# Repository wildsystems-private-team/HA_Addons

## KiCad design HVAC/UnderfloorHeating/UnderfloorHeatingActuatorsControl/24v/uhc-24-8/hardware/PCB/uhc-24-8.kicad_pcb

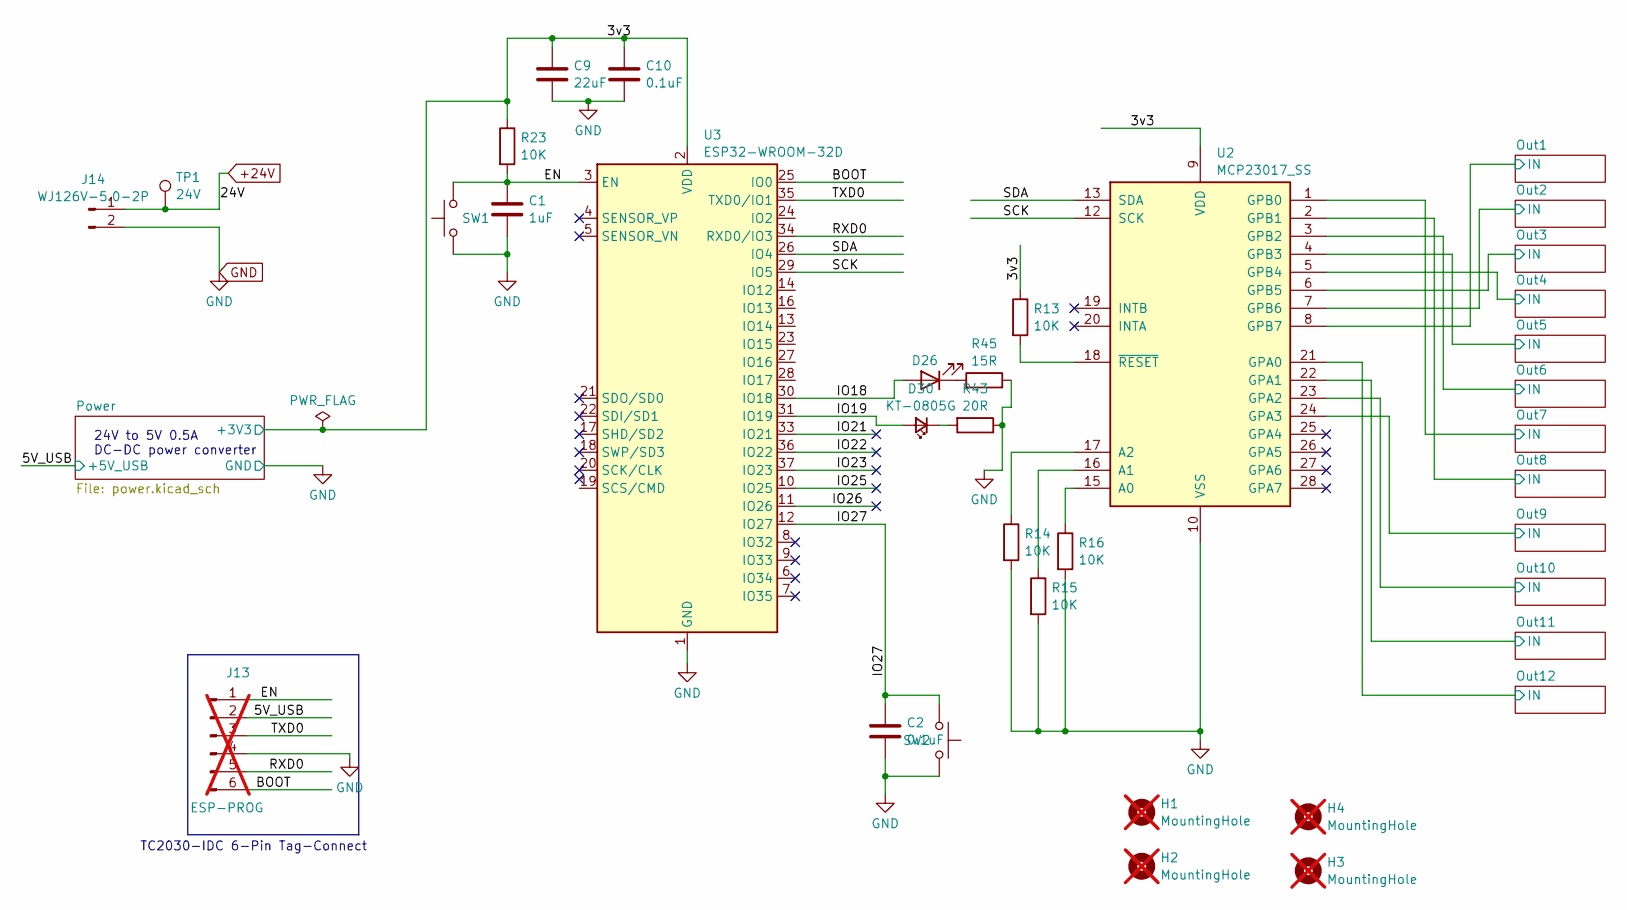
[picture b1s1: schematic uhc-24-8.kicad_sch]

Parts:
C1: 1uF; C_0402_1005Metric; LCSC Part # C14445
C2, C10: 0.1uF; C_0402_1005Metric; LCSC Part # C541406
C9: 22uF; C_0603_1608Metric; LCSC Part # C59461
D26: KT-0805B; D_0805_2012Metric; LCSC Part # C2293
D30: KT-0805G; LED_0805_2012Metric; LCSC Part # C2297
H1, H2, H3, H4: MountingHole; MountingHole_3.2mm_M3; not fitted
J13: ESP-PROG; Tag-Connect_TC2030-IDC-FP_2x03_P1.27mm_Vertical; not fitted
J14: WJ126V-5.0-2P; CONN-TH_2P-P5.08_DIBO_DB142V-5.08-2P; LCSC Part # C2898699
R13, R14, R15, R16, R23: 10K; R_0603_1608Metric; LCSC Part # C25804
R43: 20R; R_0805_2012Metric; LCSC Part # C17659
R45: 15R; R_0805_2012Metric
SW1: Reboot; SW-SMD_4P-L5.1-W5.1-P3.70-LS6.5-TL-2; LCSC Part # C318884
SW2: Clear; SW-SMD_4P-L5.1-W5.1-P3.70-LS6.5-TL-2; LCSC Part # C318884
TP1: 24V; TestPoint_Pad_D2.0mm
U2: MCP23017_SS; SSOP-28_5.3x10.2mm_P0.65mm; LCSC Part # C558584
U3: ESP32-WROOM-32D; WIFI-SMD_ESP32-WROOM-32E-A; LCSC Part # C701341

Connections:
+24V: J14.1, TP1.1; also elsewhere on the board
/3v3: C9.1, C10.1, R13.1, R23.1, U2.9 (VDD), U3.2 (VDD); also elsewhere on the board
/5V_USB: J13.2; also elsewhere on the board
/BOOT: J13.6, U3.25 (IO0)
/EN: C1.1, J13.1, R23.2, SW1.2, U3.3 (EN)
/IO18: D26.2 (A), U3.30 (IO18)
/IO19: D30.2 (A), U3.31 (IO19)
/IO21: U3.33 (IO21)
/IO22: U3.36 (IO22)
/IO23: U3.37 (IO23)
/IO25: U3.10 (IO25)
/IO26: U3.11 (IO26)
/IO27: C2.1, SW2.2, U3.12 (IO27)
/Out1/IN: U2.8 (GPB7); also elsewhere on the board
/Out2/IN: U2.7 (GPB6); also elsewhere on the board
/Out3/IN: U2.6 (GPB5); also elsewhere on the board
/Out4/IN: U2.5 (GPB4); also elsewhere on the board
/Out5/IN: U2.4 (GPB3); also elsewhere on the board
/Out6/IN: U2.3 (GPB2); also elsewhere on the board
/Out7/IN: U2.1 (GPB0); also elsewhere on the board
/Out8/IN: U2.2 (GPB1); also elsewhere on the board
/Out9/IN: U2.24 (GPA3); also elsewhere on the board
/Out10/IN: U2.23 (GPA2); also elsewhere on the board
/Out11/IN: U2.22 (GPA1); also elsewhere on the board
/Out12/IN: U2.21 (GPA0); also elsewhere on the board
/RXD0: J13.5, U3.34 (RXD0/IO3)
/SCK: U2.12 (SCK), U3.29 (IO5)
/SDA: U2.13 (SDA), U3.26 (IO4)
/TXD0: J13.3, U3.35 (TXD0/IO1)
GND: C1.2, C2.2, C9.2, C10.2, J13.4, J14.2, R14.2, R15.2, R16.2, R43.1, R45.2, SW1.1, SW2.1, U2.10 (VSS), U3.1 (GND), U3.15 (GND), U3.38 (GND), U3.39 (GND); also elsewhere on the board
unnamed: D26.1 (K), R45.1
unnamed: D30.1 (K), R43.2
unnamed: R16.1, U2.15 (A0)
unnamed: R15.1, U2.16 (A1)
unnamed: R14.1, U2.17 (A2)
unnamed: R13.2, U2.18 (~RESET)

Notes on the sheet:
24V to 5V 0.5A DC-DC power converter
TC2030-IDC 6-Pin Tag-Connect

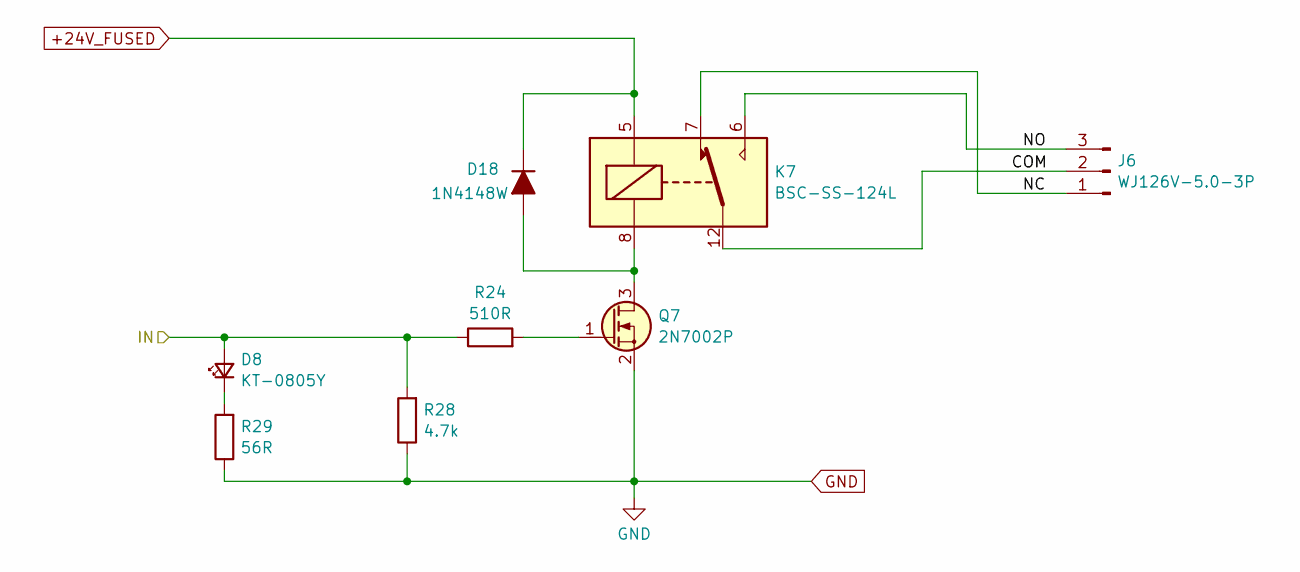
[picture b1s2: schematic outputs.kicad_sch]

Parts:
D8: KT-0805Y; LED_0805_2012Metric; LCSC Part # C2296
D18: 1N4148W; D_SOD-123; LCSC Part # C81598
J6: WJ126V-5.0-3P; CONN-TH_3P-P5.08_DIBO_DB142V-5.08-3P; LCSC Part # C2898700
K7: BSC-SS-124L; Relay_SPDT_QLRELAY_BSC; LCSC Part # C22384984
Q7: 2N7002P; SOT-23; LCSC Part # C81488
R24: 510R; R_0805_2012Metric; LCSC Part # C17734
R28: 4.7k; R_0805_2012Metric; LCSC Part # C17673
R29: 56R; R_0805_2012Metric; LCSC Part # C17757

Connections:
+24V_FUSED: D18.1 (K), K7.5; also elsewhere on the board
/Out7/COM: J6.2, K7.12
/Out7/IN: D8.2 (A), R24.1, R28.2; also elsewhere on the board
/Out7/NC: J6.1, K7.7
/Out7/NO: J6.3, K7.6
GND: Q7.2 (S), R28.1, R29.1; also elsewhere on the board
unnamed: D8.1 (K), R29.2
unnamed: D18.2 (A), K7.8, Q7.3 (D)
unnamed: Q7.1 (G), R24.2

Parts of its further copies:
D1, D2, D3, D4, D5, D6, D7, D9, D10, D11, D12: KT-0805Y; LED_0805_2012Metric; LCSC Part # C2296
D13, D14, D15, D16, D17, D19, D20, D21, D22, D23, D24: 1N4148W; D_SOD-123; LCSC Part # C81598
J1, J2, J3, J4, J5, J7, J8, J9, J10, J11, J12: WJ126V-5.0-3P; CONN-TH_3P-P5.08_DIBO_DB142V-5.08-3P; LCSC Part # C2898700
K1, K2, K3, K4, K5, K6, K8, K9, K10, K11, K12: BSC-SS-124L; Relay_SPDT_QLRELAY_BSC; LCSC Part # C22384984
Q1, Q2, Q3, Q4, Q5, Q6, Q8, Q9, Q10, Q11, Q12: 2N7002P; SOT-23; LCSC Part # C81488
R1, R6, R7, R11, R17, R20, R26, R30, R34, R36, R41: 510R; R_0805_2012Metric; LCSC Part # C17734
R2, R3, R8, R12, R19, R22, R25, R32, R35, R38, R40: 56R; R_0805_2012Metric; LCSC Part # C17757
R4, R5, R9, R10, R18, R21, R27, R31, R33, R37, R39: 4.7k; R_0805_2012Metric; LCSC Part # C17673

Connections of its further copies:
+24V_FUSED: D13.1 (K), D14.1 (K), D15.1 (K), D16.1 (K), D17.1 (K), D19.1 (K), D20.1 (K), D21.1 (K), D22.1 (K), D23.1 (K), D24.1 (K), K1.5, K2.5, K3.5, K4.5, K5.5, K6.5, K8.5, K9.5, K10.5, K11.5, K12.5; also elsewhere on the board
/Out1/COM: J1.2, K1.12
/Out1/IN: D1.2 (A), R1.1, R5.2; also elsewhere on the board
/Out1/NC: J1.1, K1.7
/Out1/NO: J1.3, K1.6
/Out2/COM: J3.2, K2.12
/Out2/IN: D2.2 (A), R4.2, R6.1; also elsewhere on the board
/Out2/NC: J3.1, K2.7
/Out2/NO: J3.3, K2.6
/Out3/COM: J2.2, K3.12
/Out3/IN: D3.2 (A), R7.1, R9.2; also elsewhere on the board
/Out3/NC: J2.1, K3.7
/Out3/NO: J2.3, K3.6
/Out4/COM: J4.2, K4.12
/Out4/IN: D4.2 (A), R11.1, R18.2; also elsewhere on the board
/Out4/NC: J4.1, K4.7
/Out4/NO: J4.3, K4.6
/Out5/COM: J5.2, K5.12
/Out5/IN: D5.2 (A), R10.2, R17.1; also elsewhere on the board
/Out5/NC: J5.1, K5.7
/Out5/NO: J5.3, K5.6
/Out6/COM: J7.2, K6.12
/Out6/IN: D6.2 (A), R20.1, R21.2; also elsewhere on the board
/Out6/NC: J7.1, K6.7
/Out6/NO: J7.3, K6.6
/Out8/COM: J8.2, K8.12
/Out8/IN: D7.2 (A), R26.1, R27.2; also elsewhere on the board
/Out8/NC: J8.1, K8.7
/Out8/NO: J8.3, K8.6
/Out9/COM: J9.2, K9.12
/Out9/IN: D9.2 (A), R30.1, R31.2; also elsewhere on the board
/Out9/NC: J9.1, K9.7
/Out9/NO: J9.3, K9.6
/Out10/COM: J10.2, K10.12
/Out10/IN: D11.2 (A), R33.2, R36.1; also elsewhere on the board
/Out10/NC: J10.1, K10.7
/Out10/NO: J10.3, K10.6
/Out11/COM: J11.2, K11.12
/Out11/IN: D10.2 (A), R34.1, R37.2; also elsewhere on the board
/Out11/NC: J11.1, K11.7
/Out11/NO: J11.3, K11.6
/Out12/COM: J12.2, K12.12
/Out12/IN: D12.2 (A), R39.2, R41.1; also elsewhere on the board
/Out12/NC: J12.1, K12.7
/Out12/NO: J12.3, K12.6
GND: Q1.2 (S), Q2.2 (S), Q3.2 (S), Q4.2 (S), Q5.2 (S), Q6.2 (S), Q8.2 (S), Q9.2 (S), Q10.2 (S), Q11.2 (S), Q12.2 (S), R2.1, R3.1, R4.1, R5.1, R8.1, R9.1, R10.1, R12.1, R18.1, R19.1, R21.1, R22.1, R25.1, R27.1, R31.1, R32.1, R33.1, R35.1, R37.1, R38.1, R39.1, R40.1; also elsewhere on the board
unnamed: D1.1 (K), R2.2
unnamed: D2.1 (K), R3.2
unnamed: D3.1 (K), R8.2
unnamed: D4.1 (K), R19.2
unnamed: D5.1 (K), R12.2
unnamed: D6.1 (K), R22.2
unnamed: D7.1 (K), R25.2
unnamed: D9.1 (K), R32.2
unnamed: D10.1 (K), R35.2
unnamed: D11.1 (K), R38.2
unnamed: D12.1 (K), R40.2
unnamed: D13.2 (A), K1.8, Q1.3 (D)
unnamed: D14.2 (A), K2.8, Q2.3 (D)
unnamed: D15.2 (A), K3.8, Q3.3 (D)
unnamed: D16.2 (A), K4.8, Q4.3 (D)
unnamed: D17.2 (A), K5.8, Q5.3 (D)
unnamed: D19.2 (A), K6.8, Q6.3 (D)
unnamed: D20.2 (A), K8.8, Q9.3 (D)
unnamed: D21.2 (A), K9.8, Q8.3 (D)
unnamed: D22.2 (A), K10.8, Q10.3 (D)
unnamed: D23.2 (A), K11.8, Q12.3 (D)
unnamed: D24.2 (A), K12.8, Q11.3 (D)
unnamed: Q1.1 (G), R1.2
unnamed: Q2.1 (G), R6.2
unnamed: Q3.1 (G), R7.2
unnamed: Q4.1 (G), R11.2
unnamed: Q5.1 (G), R17.2
unnamed: Q6.1 (G), R20.2
unnamed: Q8.1 (G), R30.2
unnamed: Q9.1 (G), R26.2
unnamed: Q10.1 (G), R36.2
unnamed: Q11.1 (G), R41.2
unnamed: Q12.1 (G), R34.2

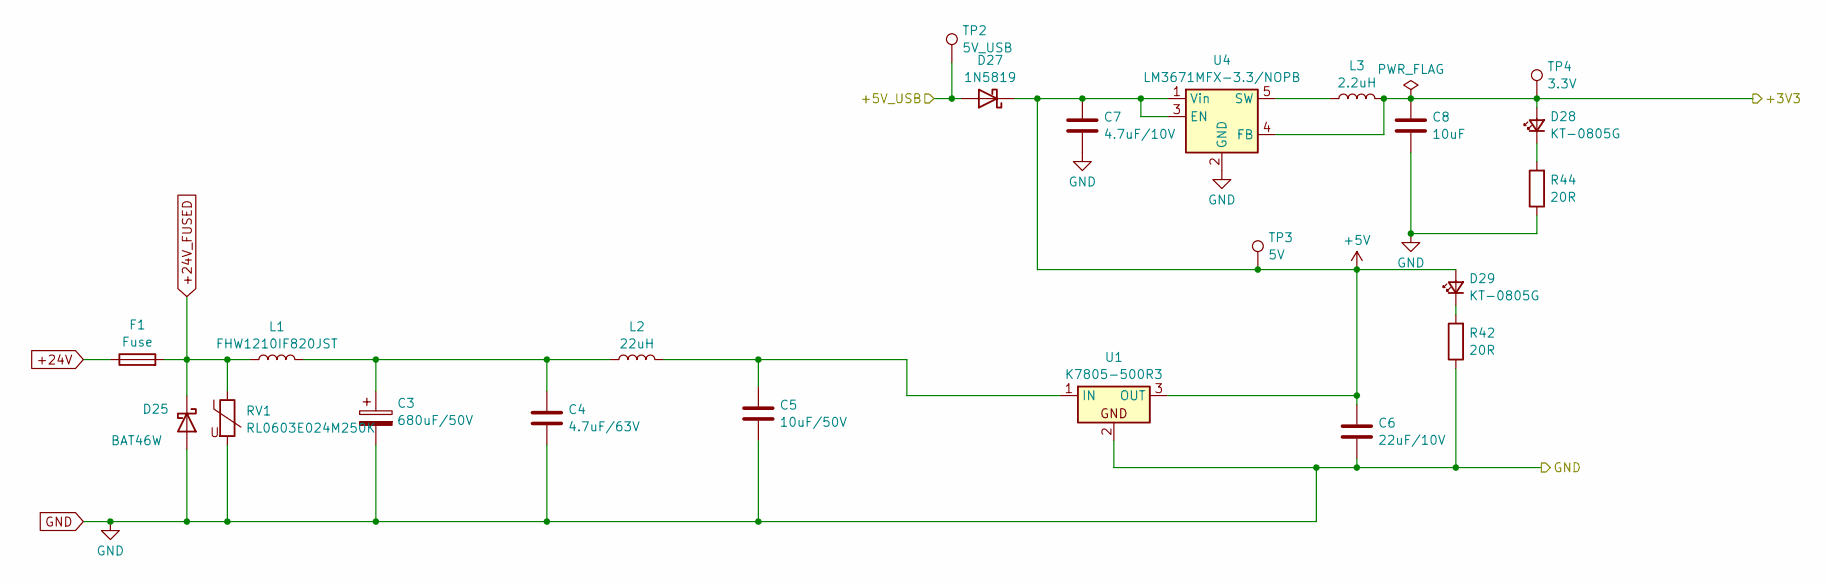
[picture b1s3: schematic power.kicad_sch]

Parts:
C3: 680uF/50V; CAP-SMD_BD12.5-L13.0-W13.0-LS14.4-FD; LCSC Part # C487372
C4: 4.7uF/63V; C_1206_3216Metric; LCSC Part # C29823
C5: 10uF/50V; C_1206_3216Metric; LCSC Part # C13585
C6: 22uF/10V; C_1206_3216Metric; LCSC Part # C5672
C7: 4.7uF/10V; C_0402_1005Metric; LCSC Part # C23733
C8: 10uF; C_0603_1608Metric; LCSC Part # C19702
D25: BAT46W; D_SOD-123; LCSC Part # C7420332
D27: 1N5819; D_SOD-123; JLCPCB Part # C3033976
D28, D29: KT-0805G; LED_0805_2012Metric; LCSC Part # C2297
F1: Fuse; FUSE-TH_L24.4-W9.4-P22.60; LCSC Part # C717030
L1: FHW1210IF820JST; L_1210_3225Metric; LCSC Part # C394099
L2: 22uH; L_0603_1608Metric; LCSC Part # C6808015
L3: 2.2uH; Ferrite_1206_3216Metric; LCSC Part # C139249
R42, R44: 20R; R_0805_2012Metric; LCSC Part # C17659
RV1: RL0603E024M250K; D_0603_1608Metric; LCSC Part # LCSC Part #
TP2: 5V_USB; TestPoint_Pad_D2.0mm
TP3: 5V; TestPoint_Pad_D2.0mm
TP4: 3.3V; TestPoint_Pad_D2.0mm
U1: K7805-500R3; PWRM-TH_K78XX-500R3; LCSC Part # C909662
U4: LM3671MFX-3.3/NOPB; TSOT-23-5; LCSC Part # C477918

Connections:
+5V: C6.1, C7.1, D27.1 (K), D29.2 (A), TP3.1, U1.3 (OUT), U4.1 (Vin), U4.3 (EN)
+24V: F1.1; also elsewhere on the board
+24V_FUSED: D25.1 (K), F1.2, L1.1, RV1.1; also elsewhere on the board
/3v3: C8.1, D28.2 (A), L3.2, TP4.1, U4.4 (FB); also elsewhere on the board
/5V_USB: D27.2 (A), TP2.1; also elsewhere on the board
GND: C3.2, C4.2, C5.2, C6.2, C7.2, C8.2, D25.2 (A), R42.1, R44.1, RV1.2, U1.2, U4.2 (GND); also elsewhere on the board
unnamed: C3.1, C4.1, L1.2, L2.1
unnamed: D28.1 (K), R44.2
unnamed: D29.1 (K), R42.2
unnamed: C5.1, L2.2, U1.1 (IN)
unnamed: L3.1, U4.5 (SW)

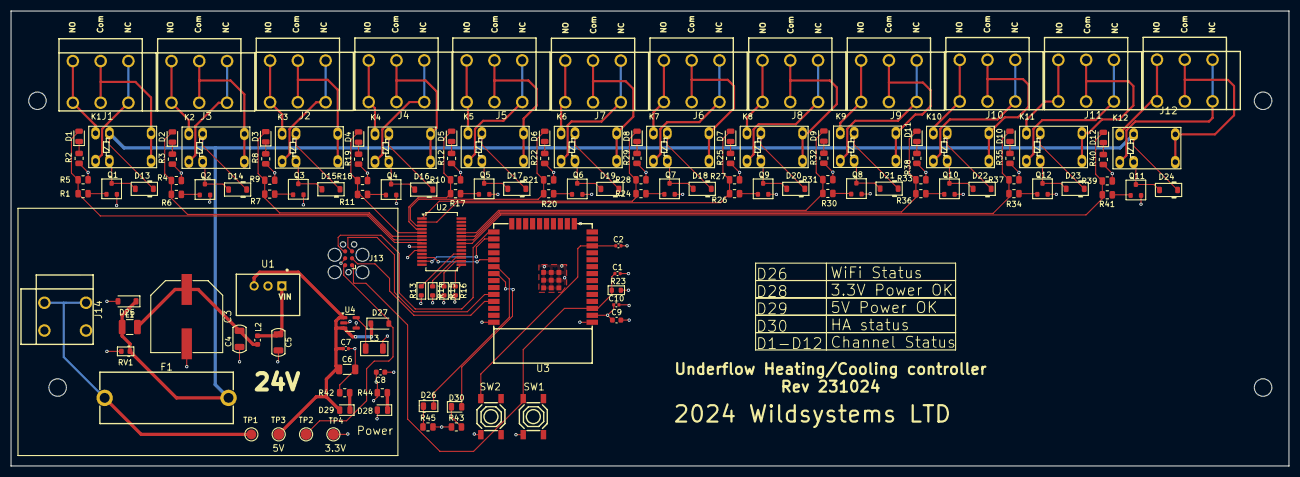
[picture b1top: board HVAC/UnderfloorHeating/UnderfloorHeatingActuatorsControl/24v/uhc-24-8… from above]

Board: 4 copper layers, 233.7 x 83.2 mm, 142 parts (0 on the bottom side), 110 nets.

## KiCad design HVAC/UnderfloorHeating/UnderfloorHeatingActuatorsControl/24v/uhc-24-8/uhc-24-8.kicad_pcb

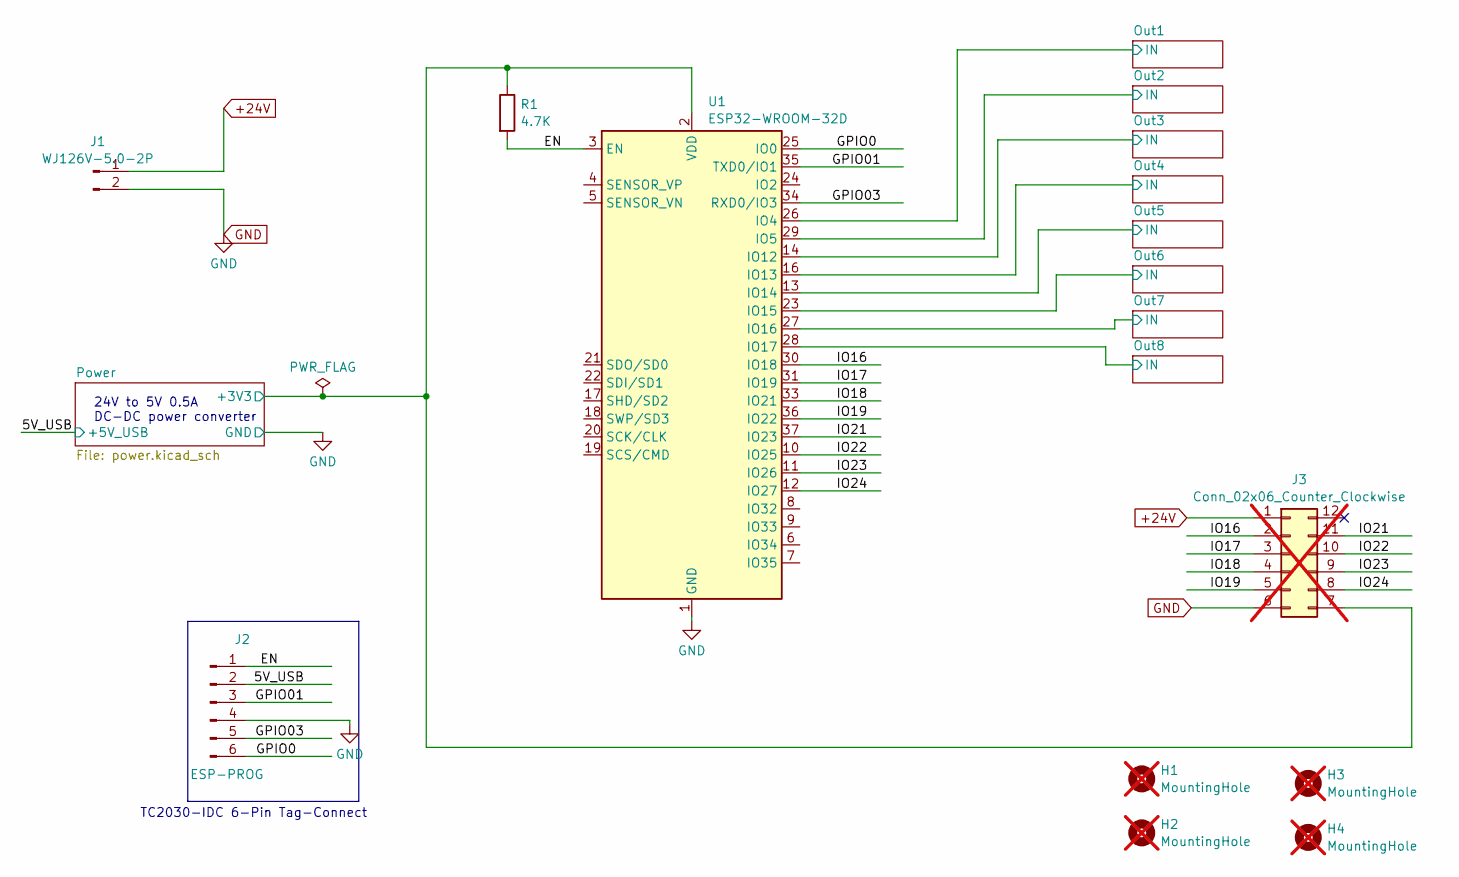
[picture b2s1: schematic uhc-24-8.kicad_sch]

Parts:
H1, H2, H3, H4: MountingHole; MountingHole_3.2mm_M3; not fitted
J1: WJ126V-5.0-2P; WJ500V-5.08-2P
J2: ESP-PROG; Tag-Connect_TC2030-IDC-FP_2x03_P1.27mm_Vertical
J3: Conn_02x06_Counter_Clockwise; Molex_Micro-Fit_3.0_43045-1212_2x06_P3.00mm_Vertical; not fitted
R1: 4.7K; R_0805_2012Metric
U1: ESP32-WROOM-32D; ESP32-WROOM-32-0.3-via

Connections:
+24V: J1.1, J3.1; also elsewhere on the board
/5V_USB: J2.2; also elsewhere on the board
/EN: J2.1, R1.2, U1.3 (EN)
/GPIO0: J2.6, U1.25 (IO0)
/GPIO01: J2.3, U1.35 (TXD0/IO1)
/GPIO03: J2.5, U1.34 (RXD0/IO3)
/IO16: J3.2, U1.30 (IO18)
/IO17: J3.3, U1.31 (IO19)
/IO18: J3.4, U1.33 (IO21)
/IO19: J3.5, U1.36 (IO22)
/IO21: J3.11, U1.37 (IO23)
/IO22: J3.10, U1.10 (IO25)
/IO23: J3.9, U1.11 (IO26)
/IO24: J3.8, U1.12 (IO27)
/Out3/IN: U1.14 (IO12); also elsewhere on the board
/Out4/IN: U1.16 (IO13); also elsewhere on the board
/Out5/IN: U1.13 (IO14); also elsewhere on the board
/Out6/IN: U1.23 (IO15); also elsewhere on the board
/Out7/IN: U1.27 (IO16); also elsewhere on the board
/Out8/IN: U1.28 (IO17); also elsewhere on the board
/Power/+3V3: J3.7, R1.1, U1.2 (VDD); also elsewhere on the board
GND: J1.2, J2.4, J3.6, U1.1 (GND), U1.15 (GND), U1.38 (GND), U1.39 (GND); also elsewhere on the board

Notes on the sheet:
24V to 5V 0.5A DC-DC power converter
TC2030-IDC 6-Pin Tag-Connect

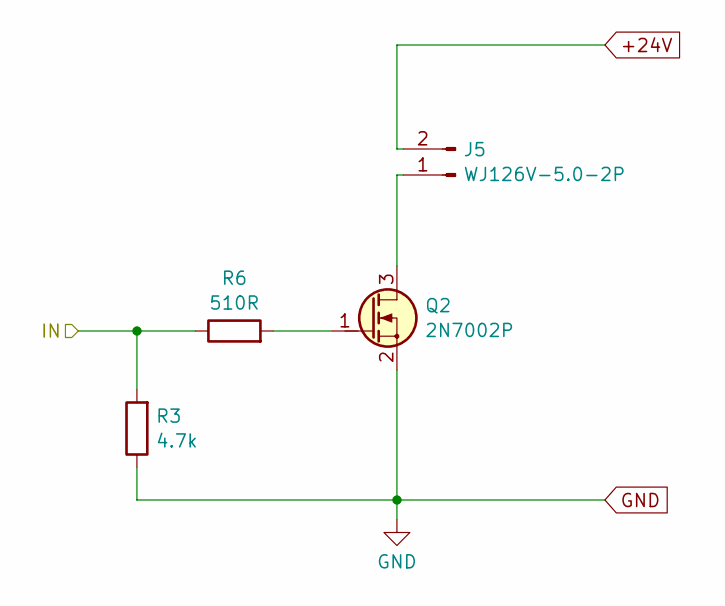
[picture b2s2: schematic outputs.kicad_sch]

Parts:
J5: WJ126V-5.0-2P; WJ500V-5.08-2P
Q2: 2N7002P; SOT-23
R3: 4.7k; R_0805_2012Metric
R6: 510R; R_0805_2012Metric

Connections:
+24V: J5.2; also elsewhere on the board
GND: Q2.2 (S), R3.1; also elsewhere on the board
unnamed: J5.1, Q2.3 (D)
unnamed: Q2.1 (G), R6.2

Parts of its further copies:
J4, J6, J7, J8, J9, J10, J11: WJ126V-5.0-2P; WJ500V-5.08-2P
Q1, Q3, Q4, Q5, Q6, Q7, Q8: 2N7002P; SOT-23
R4, R8, R10, R12, R14, R16, R18: 510R; R_0805_2012Metric
R5, R7, R9, R11, R13, R15, R17: 4.7k; R_0805_2012Metric

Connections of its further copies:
+24V: J4.2, J6.2, J7.2, J8.2, J9.2, J10.2, J11.2; also elsewhere on the board
/Out3/IN: R7.2, R8.1; also elsewhere on the board
/Out4/IN: R9.2, R10.1; also elsewhere on the board
/Out5/IN: R11.2, R12.1; also elsewhere on the board
/Out6/IN: R13.2, R14.1; also elsewhere on the board
/Out7/IN: R15.2, R16.1; also elsewhere on the board
/Out8/IN: R17.2, R18.1; also elsewhere on the board
GND: Q1.2 (S), Q3.2 (S), Q4.2 (S), Q5.2 (S), Q6.2 (S), Q7.2 (S), Q8.2 (S), R5.1, R7.1, R9.1, R11.1, R13.1, R15.1, R17.1; also elsewhere on the board
unnamed: J4.1, Q1.3 (D)
unnamed: J6.1, Q3.3 (D)
unnamed: J7.1, Q4.3 (D)
unnamed: J8.1, Q5.3 (D)
unnamed: J9.1, Q6.3 (D)
unnamed: J10.1, Q7.3 (D)
unnamed: J11.1, Q8.3 (D)
unnamed: Q1.1 (G), R4.2
unnamed: Q3.1 (G), R8.2
unnamed: Q4.1 (G), R10.2
unnamed: Q5.1 (G), R12.2
unnamed: Q6.1 (G), R14.2
unnamed: Q7.1 (G), R16.2
unnamed: Q8.1 (G), R18.2

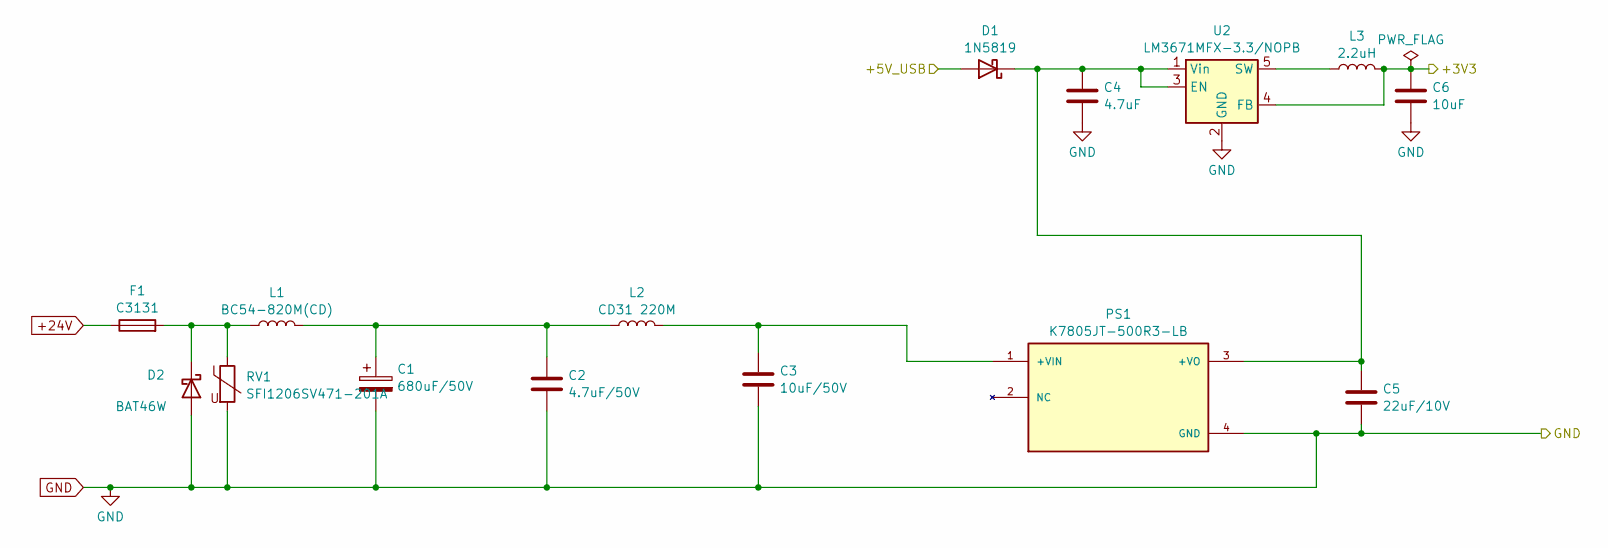
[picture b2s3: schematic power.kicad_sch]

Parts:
C1: 680uF/50V; CP_Radial_D12.5mm_P5.00mm
C2: 4.7uF/50V; C_Radial_D4.0mm_H5.0mm_P1.50mm
C3: 10uF/50V; C_Radial_D5.0mm_H11.0mm_P2.00mm
C4: 4.7uF; C_0805_2012Metric
C5: 22uF/10V; C_Radial_D4.0mm_H7.0mm_P1.50mm
C6: 10uF; C_0805_2012Metric
D1: 1N5819; D_SOD-323; JLCPCB Part # C3033976
D2: BAT46W; D_SOD-123
F1: C3131; Fuseholder_Cylinder-5x20mm_Schurter_0031_8201_Horizontal_Op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
L1: BC54-820M(CD); BC54-820M
L2: CD31 220M; CD31
L3: 2.2uH; L_0805_2012Metric
PS1: K7805JT-500R3-LB; CONV_K7805JT-500R3-LB; PARTREV 2022.07.25-A/4
RV1: SFI1206SV471-201A; R_1206_3216Metric
U2: LM3671MFX-3.3/NOPB; TSOT-23-5

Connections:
+24V: F1.1; also elsewhere on the board
/5V_USB: D1.2 (A); also elsewhere on the board
/Power/+3V3: C6.1, L3.2, U2.4 (FB); also elsewhere on the board
GND: C1.2, C2.2, C3.2, C4.2, C5.2, C6.2, D2.2 (A), PS1.4 (GND), RV1.2, U2.2 (GND); also elsewhere on the board
unnamed: C1.1, C2.1, L1.2, L2.1
unnamed: C4.1, C5.1, D1.1 (K), PS1.3 (+VO), U2.1 (Vin), U2.3 (EN)
unnamed: D2.1 (K), F1.2, L1.1, RV1.1
unnamed: C3.1, L2.2, PS1.1 (+VIN)
unnamed: L3.1, U2.5 (SW)

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
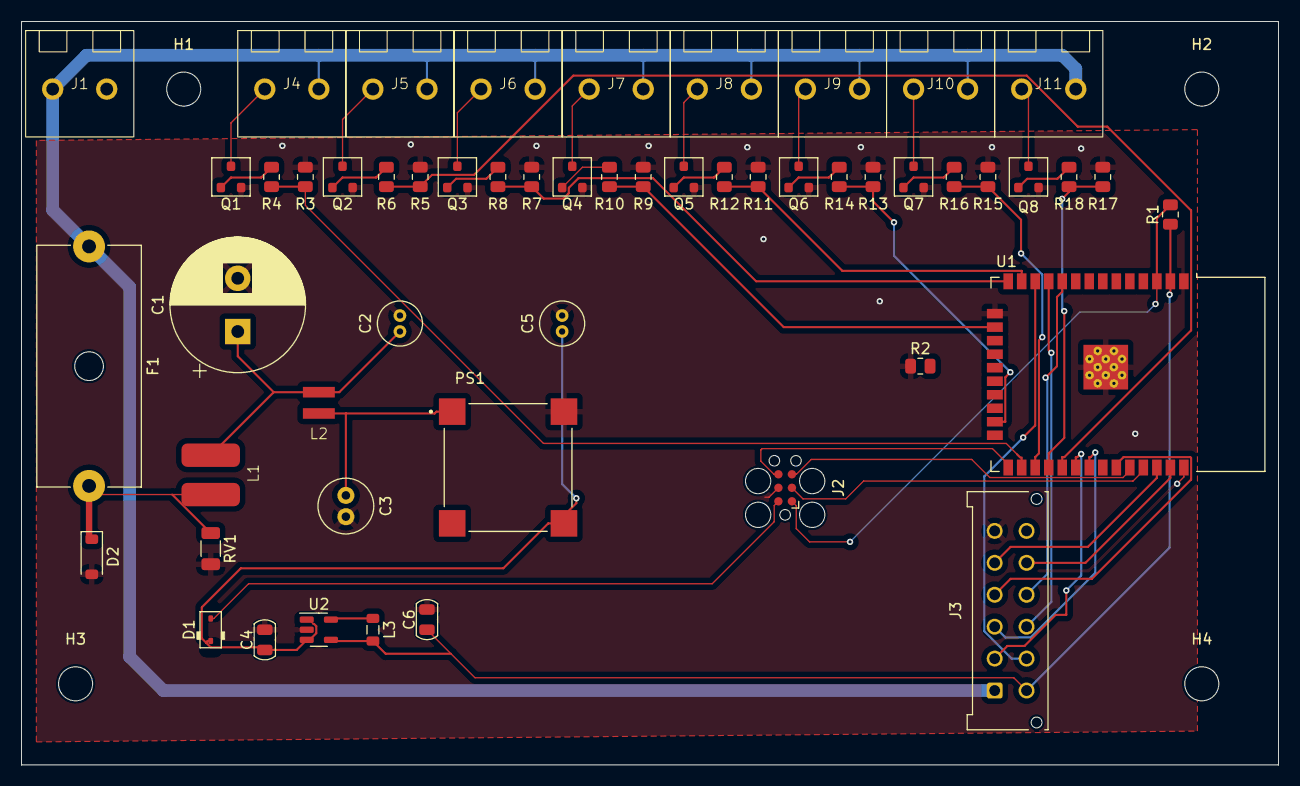
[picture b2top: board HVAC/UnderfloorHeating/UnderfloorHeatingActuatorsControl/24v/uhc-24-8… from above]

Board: 2 copper layers, 118.1 x 69.8 mm, 57 parts (0 on the bottom side), 45 nets.

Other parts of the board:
R2: 4.7k; R_0805_2012Metric

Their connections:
GND: R2.1; also elsewhere on the board

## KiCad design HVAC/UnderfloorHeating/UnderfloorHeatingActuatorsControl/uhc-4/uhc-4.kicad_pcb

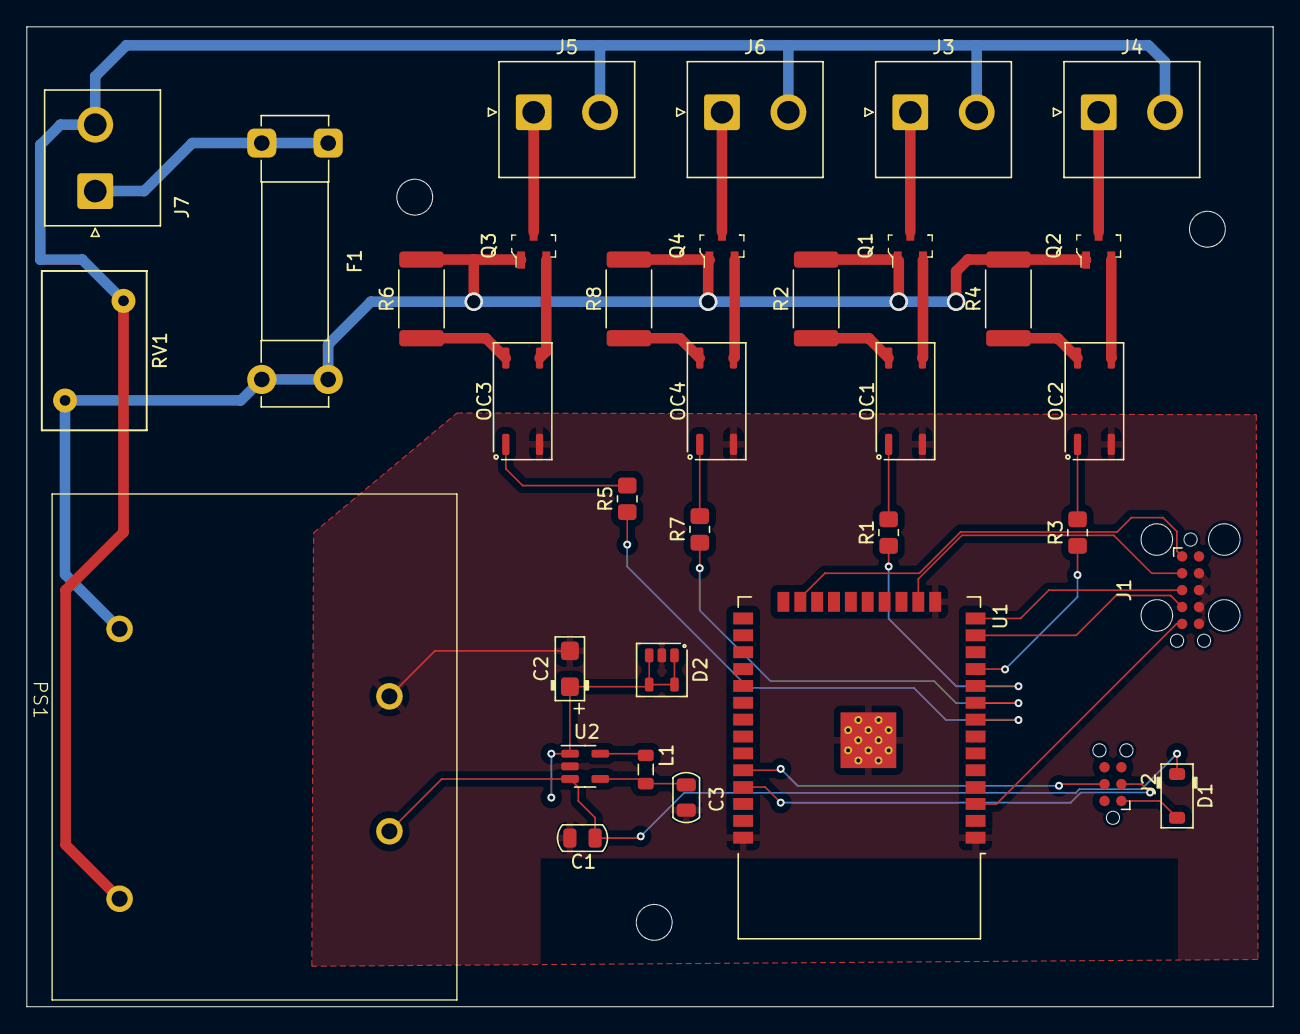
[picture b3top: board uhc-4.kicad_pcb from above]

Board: 2 copper layers, 93.9 x 73.8 mm, 34 parts (0 on the bottom side), 35 nets.

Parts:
C1: 4.7uF; C_0805_2012Metric
C2: TAJA105K025RNJ; CP_EIA-3216-18_Kemet-A
C3: 10uF; C_0805_2012Metric
D1: 1N5819; D_SOD-123
D2: ESDA5V3SC5; SOT-23-5
F1: 2A/250V/FH-1096; Fuseholder_Clip-5x20mm_Bel_FC-203-22_Lateral_P17.80x5.00mm_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
J1: JTAG; Tag-Connect_TC2050-IDC-FP_2x05_P1.27mm_Vertical
J2: RS-232; Tag-Connect_TC2030-IDC-NL_2x03_P1.27mm_Vertical
J3: Out3; JST_NV_B02P-NV_1x02_P5.00mm_Vertical
J4: Out4; JST_NV_B02P-NV_1x02_P5.00mm_Vertical
J5: Out1; JST_NV_B02P-NV_1x02_P5.00mm_Vertical
J6: Out2; JST_NV_B02P-NV_1x02_P5.00mm_Vertical
J7: 220IN; JST_NV_B02P-NV_1x02_P5.00mm_Vertical
L1: 2.2uH; L_0805_2012Metric
OC1, OC2, OC3, OC4: TLP266J; SOIC-4_4.55x3.7mm_P2.54mm
PS1: ZP05S0500WB; ZP05SXX00WB
Q1, Q2, Q3, Q4: MAC97A8; SOT-23-3
R1, R3, R5, R7: 91; R_0805_2012Metric_Pad1.20x1.40mm_HandSolder
R2, R4, R6, R8: 300/1w; R_2512_6332Metric
RV1: S10K460; RV_Disc_D12mm_W7.9mm_P7.5mm
U1: ESP32-WROOM-32
U2: LM3671MFX-3.3/NOPB; TSOT-23-5

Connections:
/ESP_EN: J1.5, U1.3 (EN)
/GPIO01: J2.3, U1.35 (TXD0/IO1)
/GPIO03: J2.4, U1.34 (RXD0/IO3)
/GPIO12: J1.3, U1.14 (IO12)
/GPIO13: J1.2, U1.16 (IO13)
/GPIO14: J1.4, U1.13 (IO14)
/GPIO15: J1.1, U1.23 (IO15)
/Out1: R5.1, U1.8 (IO32)
/Out2: R7.1, U1.9 (IO33)
/Out3: R1.1, U1.10 (IO25)
/Out4: R3.1, U1.11 (IO26)
/Power/3v3: C3.1, L1.2, U2.4 (FB)
/Power/+5V_USB: D1.2 (A), J2.1
/Power/L: F1.1, J7.1
/PowerOut1/220V_out: J4.1, Q2.3 (A1)
/PowerOut2/220V_out: J5.1, Q3.3 (A1)
/PowerOut3/220V_out: J6.1, Q4.3 (A1)
/PowerOut/220V_out: J3.1, Q1.3 (A1)
Fused L: F1.2, PS1.1 (AC/L), Q1.1 (A2), Q2.1 (A2), Q3.1 (A2), Q4.1 (A2), R2.2, R4.2, R6.2, R8.2, RV1.1
GND: C1.2, C2.2, C3.2, D2.2 (VN), J1.6, J1.7, J1.8, J1.9, OC1.3, OC2.3, OC3.3, OC4.3, PS1.3 (-Vout), U1.1 (GND), U1.15 (GND), U1.38 (GND), U1.39 (GND), U2.2 (GND)
N: J3.2, J4.2, J5.2, J6.2, J7.2, PS1.2 (AC/N), RV1.2
unnamed: C1.1, C2.1, D1.1 (K), D2.1 (L1), D2.3 (L2), D2.4 (L3), D2.5 (L4), PS1.4 (+Vout), U2.1 (Vin), U2.3 (EN)
unnamed: OC1.1, R1.2
unnamed: OC1.6, R2.1
unnamed: OC2.1, R3.2
unnamed: OC2.6, R4.1
unnamed: OC3.1, R5.2
unnamed: OC3.6, R6.1
unnamed: OC4.1, R7.2
unnamed: OC4.6, R8.1
unnamed: OC1.4, Q1.2 (G)
unnamed: OC2.4, Q2.2 (G)
unnamed: OC3.4, Q3.2 (G)
unnamed: OC4.4, Q4.2 (G)
unnamed: L1.1, U2.5 (SW)

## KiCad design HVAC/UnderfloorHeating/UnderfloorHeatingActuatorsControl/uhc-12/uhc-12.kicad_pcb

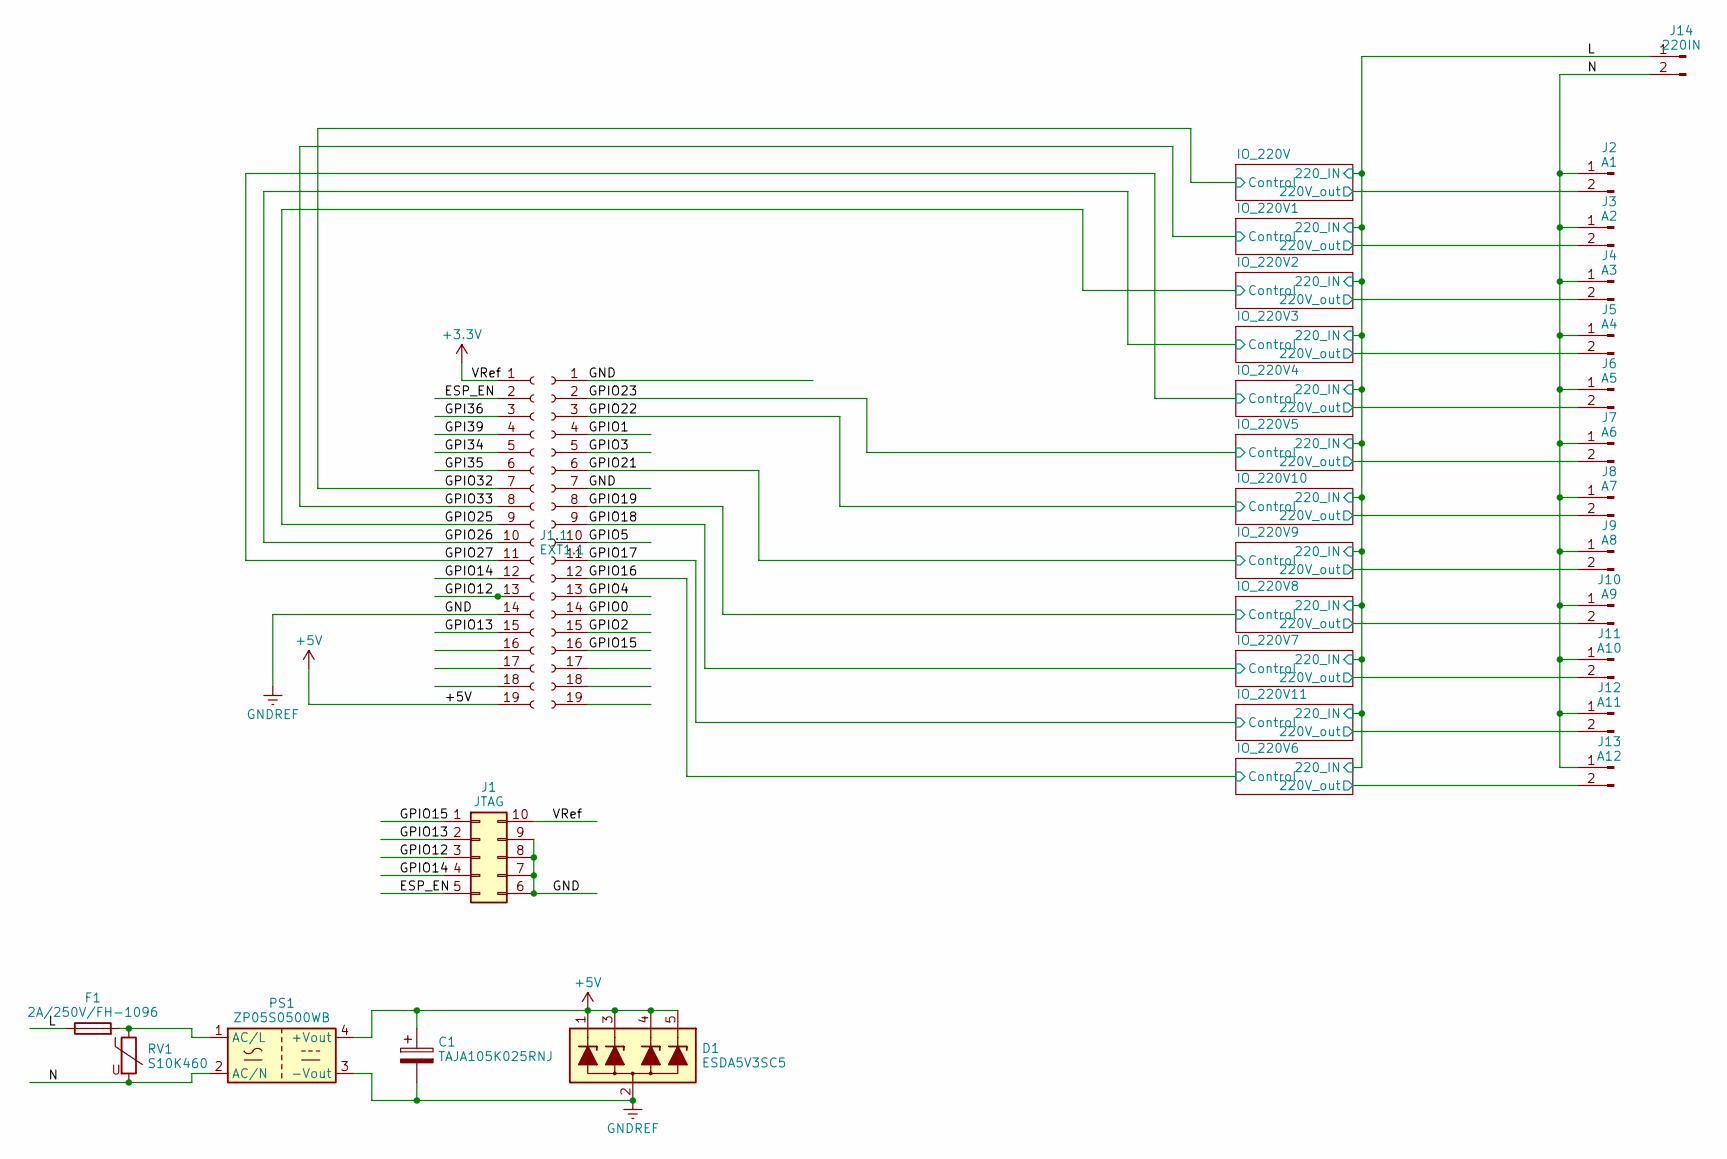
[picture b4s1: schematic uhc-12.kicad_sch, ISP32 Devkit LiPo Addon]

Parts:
C1: TAJA105K025RNJ; CP_EIA-3216-18_Kemet-A
D1: ESDA5V3SC5; SOT-23-5
F1: 2A/250V/FH-1096; Fuseholder_Clip-5x20mm_Bel_FC-203-22_Lateral_P17.80x5.00mm_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
J1: JTAG; Tag-Connect_TC2050-IDC-FP_2x05_P1.27mm_Vertical
J1.1: EXT1.1; PinHeader_1x19_P2.54mm_Vertical
J1.2: EXT1.2; PinHeader_1x19_P2.54mm_Vertical
J2: A1; DG500-5.0-02P
J3: A2; DG500-5.0-02P
J4: A3; DG500-5.0-02P
J5: A4; DG500-5.0-02P
J6: A5; DG500-5.0-02P
J7: A6; DG500-5.0-02P
J8: A7; DG500-5.0-02P
J9: A8; DG500-5.0-02P
J10: A9; DG500-5.0-02P
J11: A10; DG500-5.0-02P
J12: A11; DG500-5.0-02P
J13: A12; DG500-5.0-02P
J14: 220IN; DG500-5.0-02P
PS1: ZP05S0500WB; ZP05SXX00WB
RV1: S10K460; RV_Disc_D12mm_W7.9mm_P7.5mm

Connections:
+3.3V: J1.10, J1.1.1
+5V: C1.1, D1.1 (L1), D1.3 (L2), D1.4 (L3), D1.5 (L4), J1.1.19, PS1.4 (+Vout)
/ESP_EN: J1.5, J1.1.2
/GPI34: J1.1.5
/GPI35: J1.1.6
/GPI36: J1.1.3
/GPI39: J1.1.4
/GPIO0: J1.2.14
/GPIO1: J1.2.4
/GPIO2: J1.2.15
/GPIO3: J1.2.5
/GPIO4: J1.2.13
/GPIO5: J1.2.10
/GPIO12: J1.3, J1.1.13
/GPIO13: J1.2, J1.1.15
/GPIO14: J1.4, J1.1.12
/GPIO15: J1.1, J1.2.16
/GPIO16: J1.2.12; also elsewhere on the board
/GPIO17: J1.2.11; also elsewhere on the board
/GPIO18: J1.2.9; also elsewhere on the board
/GPIO19: J1.2.8; also elsewhere on the board
/GPIO21: J1.2.6; also elsewhere on the board
/GPIO22: J1.2.3; also elsewhere on the board
/GPIO23: J1.2.2; also elsewhere on the board
/GPIO25: J1.1.9; also elsewhere on the board
/GPIO26: J1.1.10; also elsewhere on the board
/GPIO27: J1.1.11; also elsewhere on the board
/GPIO32: J1.1.7; also elsewhere on the board
/GPIO33: J1.1.8; also elsewhere on the board
/IO_220V1/220V_out: J3.2; also elsewhere on the board
/IO_220V2/220V_out: J4.2; also elsewhere on the board
/IO_220V3/220V_out: J5.2; also elsewhere on the board
/IO_220V4/220V_out: J6.2; also elsewhere on the board
/IO_220V5/220V_out: J7.2; also elsewhere on the board
/IO_220V6/220V_out: J13.2; also elsewhere on the board
/IO_220V7/220V_out: J11.2; also elsewhere on the board
/IO_220V8/220V_out: J10.2; also elsewhere on the board
/IO_220V9/220V_out: J9.2; also elsewhere on the board
/IO_220V10/220V_out: J8.2; also elsewhere on the board
/IO_220V11/220V_out: J12.2; also elsewhere on the board
/IO_220V/220V_out: J2.2; also elsewhere on the board
/L: F1.1, J14.1; also elsewhere on the board
/N: J2.1, J3.1, J4.1, J5.1, J6.1, J7.1, J8.1, J9.1, J10.1, J11.1, J12.1, J13.1, J14.2, PS1.2 (AC/N), RV1.2
GNDREF: C1.2, D1.2 (VN), J1.6, J1.7, J1.8, J1.9, J1.1.14, J1.2.1, J1.2.7, PS1.3 (-Vout); also elsewhere on the board
unnamed: F1.2, PS1.1 (AC/L), RV1.1
